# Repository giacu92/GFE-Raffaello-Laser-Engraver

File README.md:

# GFE-Raffaello-Laser-Engraver
This repo contains all the files of my Arduino Nano based Laser Engraver firmware for Arduino.

* Author: Giacomo Mammarella
* email: giacomo.mammarella@student.univaq.it

# File list:
* [grbl09j_GFE.hex](https://github.com/giacu92/GFE-Raffaello-Laser-Engraver/blob/master/grbl09j_GFE.hex): is the hex file precompiled for my Arduino Nano controller Board.
* [Laser engraver V2.sch](https://github.com/giacu92/GFE-Raffaello-Laser-Engraver/blob/master/Laser%20engraver%20V2.sch): the Cadsoft Eagle 6.5 schematic file for the board.
* [Laser engraver V2.brd](https://github.com/giacu92/GFE-Raffaello-Laser-Engraver/blob/master/Laser%20engraver%20V2.brd): the Cadsoft Eagle 6.5 board file.
* Nano grbl.png: useful as connections reference guide.

# .hex file characteristics: grbl09j_GFE.hex 
* Changed defaults for the GFE Raffaello Laser Engraver to match motor and machine parameters.
* Changed homing cycle: $H now ignores the z-axis and perform homing cycle for 2 axis machines.
* Mapped PWM Spindle control (pin: D11) on the range from 0 (1/255, Laser still ON!) to 12.000 (DC). The value 12.000 was chosen to match bCNC parameter for spindle max speed. 

# Realize the board, BOM:
To realize the board you'll need the following parts. And the links to buy 'em:
* [Arduino Nano Compatible board](http://www.banggood.com/ATmega328P-Arduino-Compatible-Nano-V3-Improved-Version-With-USB-Cable-p-933647.html) from Banggood.com
* [Mini DC-DC Converter](http://www.banggood.com/Mini-DC-DC-Converter-Step-Down-Module-Adjustable-Power-Supply-p-920327.html) from Banggood.com
* 2 x [A4988 Stepper Driver](http://www.banggood.com/5Pcs-3D-Printer-A4988-Reprap-Stepper-Motor-Driver-Module-p-952527.html) i got mine from Banggood.com too, bought in pack of 5 for about $8,00.
* 2 x [3 poles DIP Switches](http://www.aliexpress.com/item/DIP-switch-3-way-2-54mm-DIP-Switches-3P/939142709.html) from Aliexpress.com
* 1 x [2.1mm DC Jack Female Plug Connector](http://www.aliexpress.com/item/DC-Power-adapter-dc-jack-connector-DC005-5-5-X-2-1-mm-50-pcs-lot/32352870494.html?spm=2114.01020208.3.19.BoIzX5&ws_ab_test=searchweb201556_3,searchweb201644_2_10001_10002_10005_10006_10003_10004_62,searchweb201560_6,searchweb1451318400_6149), but I got mine from a local Hardware Store
* 2 x 100uF/25V Electrolitic Capacitor from Hardware Store
* 3mm red led, 1N4001 diode and a 4,7k resistor for the led.

# Connections:

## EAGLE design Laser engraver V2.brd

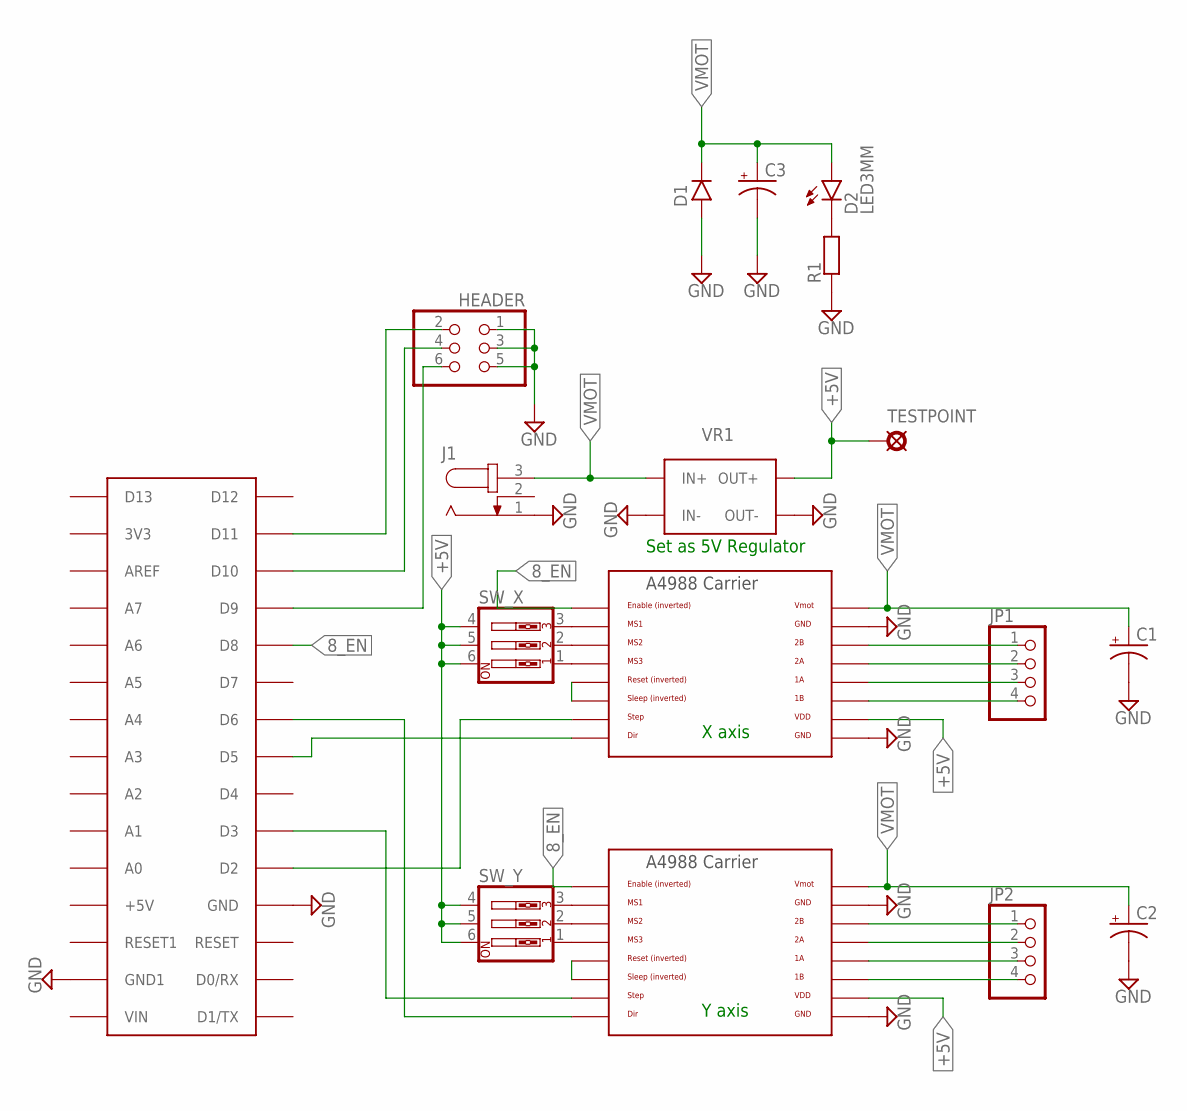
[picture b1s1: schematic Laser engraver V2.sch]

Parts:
C1, C2: 0501; 050_020_1
C3: 0631; 063_025
D1: 1N400X.3; DO41-3
D2: LED3MM
HEADER: PINHD-2X3; 2X03
J1: JACK-PLUG0; SPC4077
JP1, JP2: PINHD-1X4; 1X04
MOTOR_X: A4988BREAKOUT
MOTOR_Y: A4988BREAKOUT
R1: 6MM-EU; R0207/3
SW_X: SW_DIP-3; EDG-03
SW_Y: SW_DIP-3; EDG-03
TESTPOINT: PAD; SQUARE
U$3: ARDUINONANO; PDIP-32
VR1: VOLTAGE_REG_BANGGOOD; VOLTAGE_REG

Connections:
8_EN: MOTOR_X.EN, MOTOR_Y.EN, U$3.D8
+5V: MOTOR_X.VDD, MOTOR_Y.VDD, SW_X.4, SW_X.5, SW_X.6, SW_Y.4, SW_Y.5, SW_Y.6, TESTPOINT.1, VR1.O+1 (OUT+), VR1.O+2 (OUT+)
GND: C1.-, C2.-, C3.-, D1.A, HEADER.1, HEADER.3, HEADER.5, J1.1, MOTOR_X.GND, MOTOR_X.GND@0 (GND), MOTOR_Y.GND, MOTOR_Y.GND@0 (GND), R1.1, U$3.GND, U$3.GND1, VR1.IN-1 (IN-), VR1.IN-2 (IN-), VR1.O-1 (OUT-), VR1.O-2 (OUT-)
unnamed: MOTOR_X.MS3, SW_X.1
unnamed: MOTOR_X.MS2, SW_X.2
unnamed: MOTOR_X.MS1, SW_X.3
unnamed: MOTOR_Y.MS3, SW_Y.1
unnamed: MOTOR_Y.MS2, SW_Y.2
unnamed: MOTOR_Y.MS1, SW_Y.3
unnamed: HEADER.6, U$3.D9
unnamed: MOTOR_X.DIR, U$3.D5
unnamed: MOTOR_X.STEP, U$3.D2
unnamed: MOTOR_Y.DIR, U$3.D6
unnamed: MOTOR_Y.STEP, U$3.D3
unnamed: MOTOR_Y.RST, MOTOR_Y.SLP (SLEEP)
unnamed: MOTOR_X.RST, MOTOR_X.SLP (SLEEP)
unnamed: HEADER.4, U$3.D10
unnamed: HEADER.2, U$3.D11
unnamed: JP1.1, MOTOR_X.2B
unnamed: D2.K (C), R1.2
unnamed: JP1.4, MOTOR_X.1B
unnamed: JP1.3, MOTOR_X.1A
unnamed: JP1.2, MOTOR_X.2A
unnamed: JP2.1, MOTOR_Y.2B
unnamed: JP2.2, MOTOR_Y.2A
unnamed: JP2.3, MOTOR_Y.1A
unnamed: JP2.4, MOTOR_Y.1B
VMOT: C1.+, C2.+, C3.+, D1.C, D2.A, J1.3, MOTOR_X.VMOT, MOTOR_Y.VMOT, VR1.IN+1 (IN+), VR1.IN+2 (IN+)

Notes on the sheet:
X axis
Y axis
Set as 5V Regulator

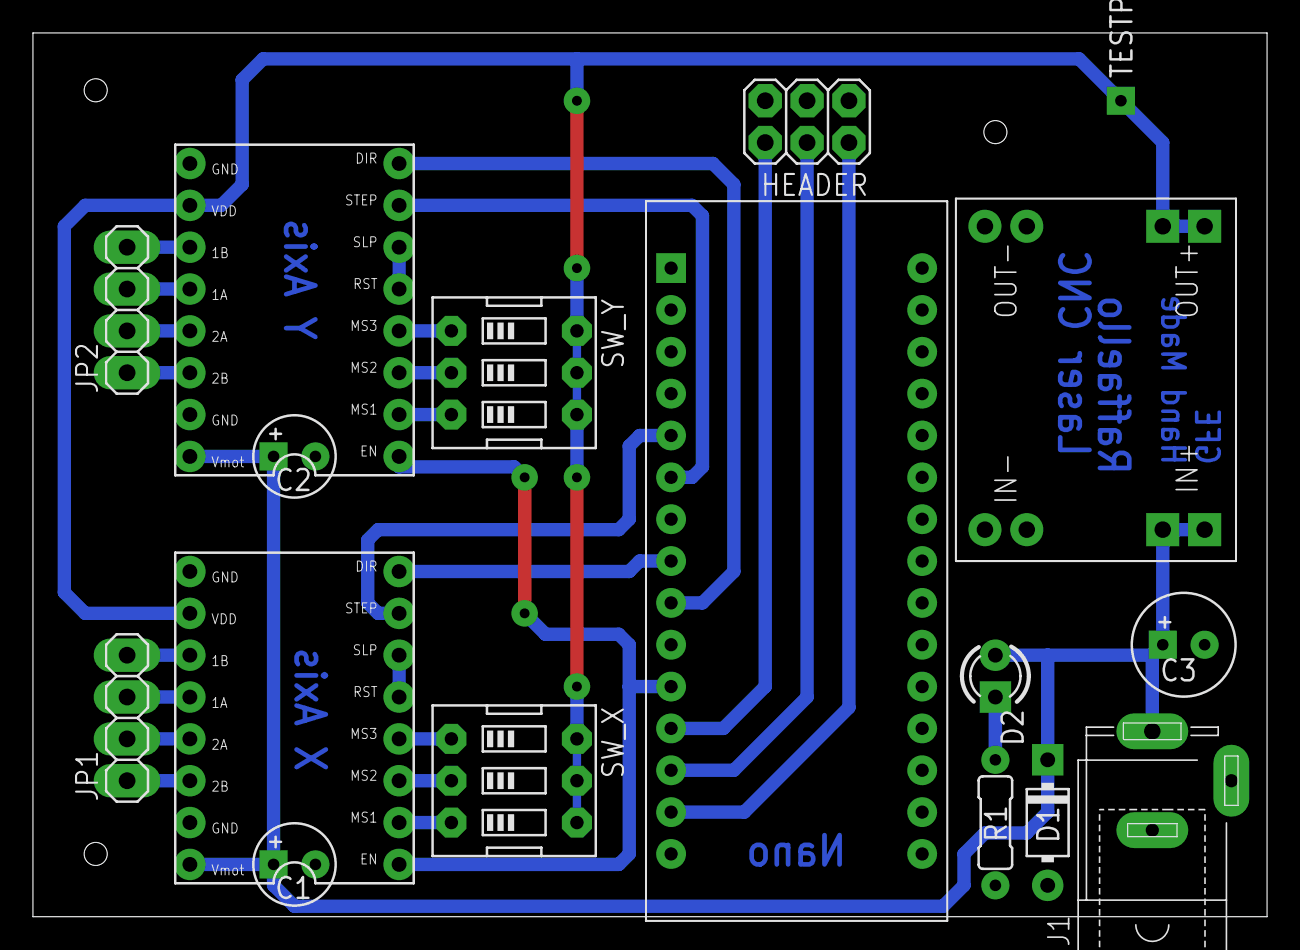
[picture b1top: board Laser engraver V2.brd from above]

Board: 2 copper layers, 74.9 x 53.6 mm, 17 parts (0 on the bottom side), 28 nets.

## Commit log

2016-01-07 grbl based hex file of my Raffaello Laser Engraver. It has the following options: Homing ignores the Z-axis Spindle PWM set as 100% when at 12000rpm on bCNC
2016-01-07 eagle files
2016-01-07 Eagle 6.5 schematic file
2016-01-07 Eagle 6.5 board file
2016-01-07 Arduino Nano configuration of 0.9j_GFE.hex firmware
2016-01-07 Hex file for grbl 0.9j_GFE. Added default_GFE.h eeprom settings
